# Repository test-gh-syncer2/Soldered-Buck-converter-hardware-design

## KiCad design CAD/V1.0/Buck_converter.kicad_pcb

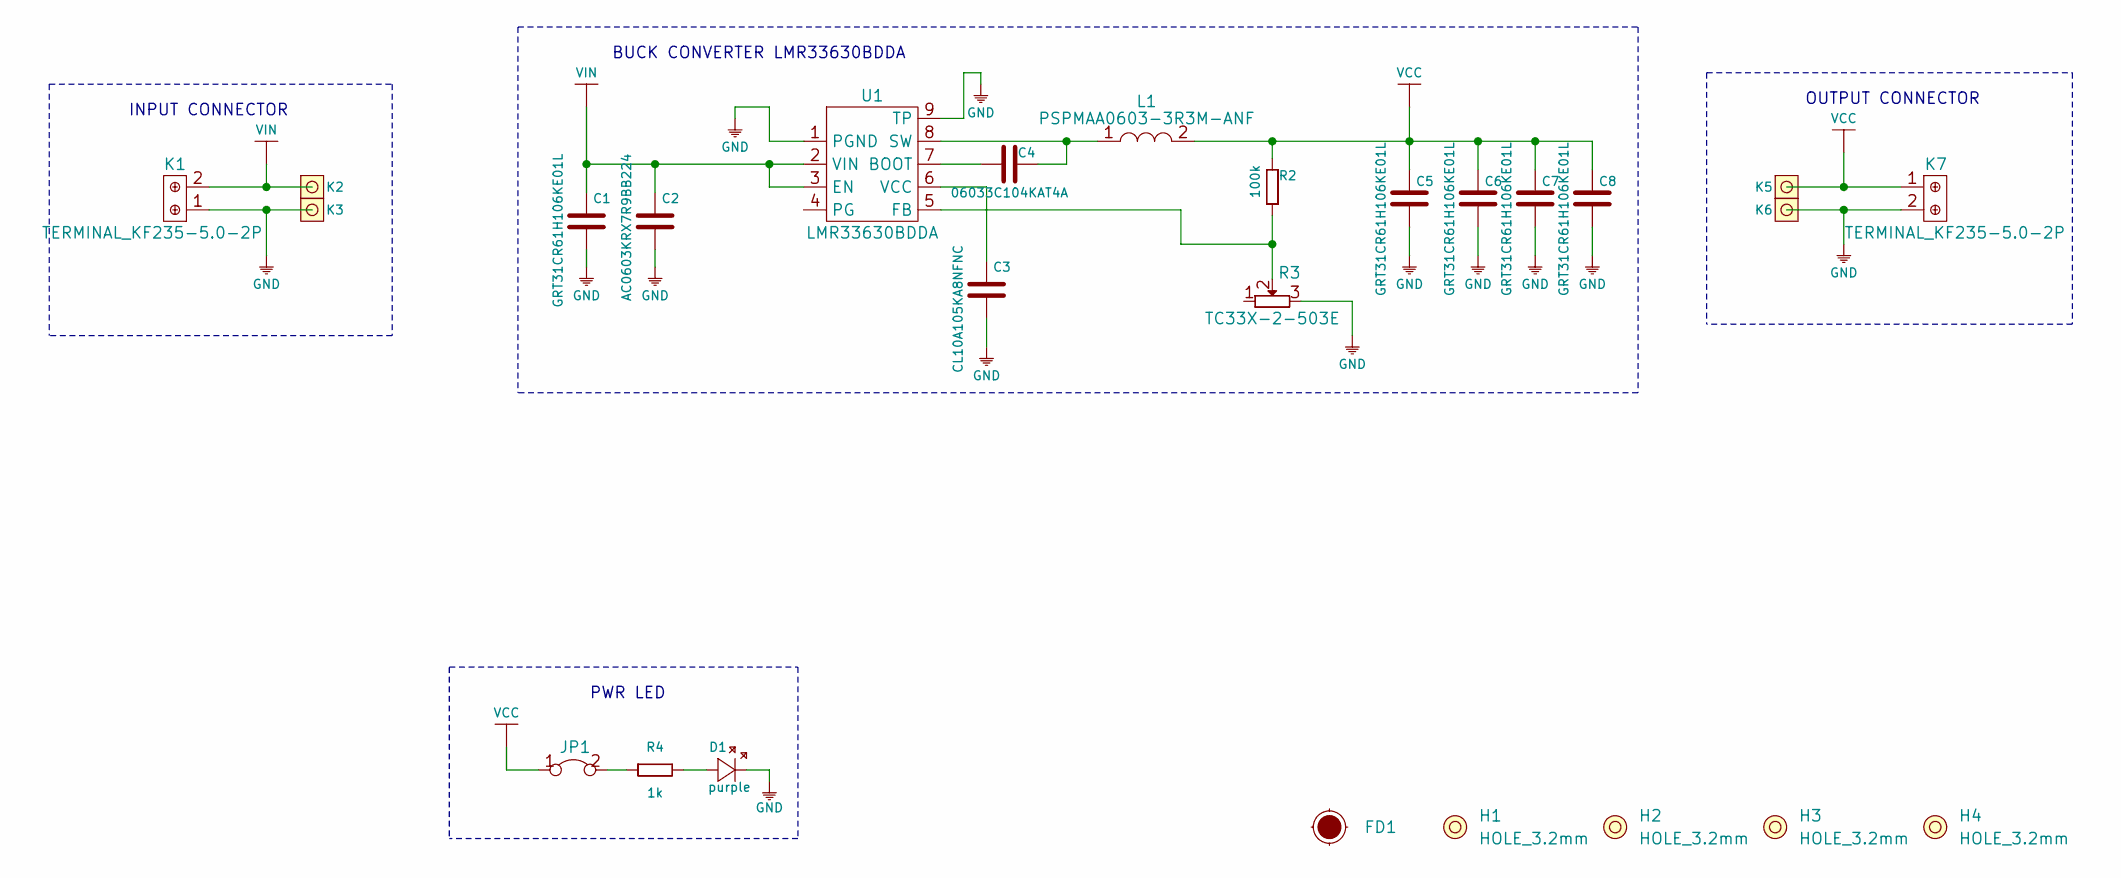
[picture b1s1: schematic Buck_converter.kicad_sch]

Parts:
C1, C5, C6, C7, C8: GRT31CR61H106KE01L; 1206C
C2: AC0603KRX7R9BB224; 0603C
C3: CL10A105KA8NFNC; 0603C
C4: 06033C104KAT4A; 0603C
D1: purple; 0402LED
FD1: Fiducial_Stencil; FIDUCIAL_1MM_PASTE
H1, H2, H3, H4: HOLE_3.2mm
JP1: SMD-JUMPER-CONNECTED_TRACE_NOSLODERMASK
K1, K7: TERMINAL_KF235-5.0-2P
K2, K3, K5, K6: HEADER_MALE_1X1
L1: PSPMAA0603-3R3M-ANF; Inductor_SMD_7x6.6
R2: 100k; 0603R
R3: TC33X-2-503E; tc33x-2-103e
R4: 1k; 0402R
U1: LMR33630BDDA; SOIC-8_POWERPAD

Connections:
GND: C1.1, C2.1, C3.1, C5.1, C6.1, C7.1, C8.1, D1.2 (K), K1.1, K3.1, K6.1, K7.2, R3.3, U1.1 (PGND), U1.9 (TP)
unnamed: C3.2, U1.6 (VCC)
unnamed: C4.1, U1.7 (BOOT)
unnamed: C4.2, L1.1, U1.8 (SW)
unnamed: D1.1 (A), R4.2
unnamed: JP1.2, R4.1
unnamed: R2.1, R3.2, U1.5 (FB)
VCC: C5.2, C6.2, C7.2, C8.2, JP1.1, K5.1, K7.1, L1.2, R2.2
VIN: C1.2, C2.2, K1.2, K2.1, U1.2 (VIN), U1.3 (EN)

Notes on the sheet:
INPUT CONNECTOR
PWR LED
BUCK CONVERTER LMR33630BDDA
OUTPUT CONNECTOR

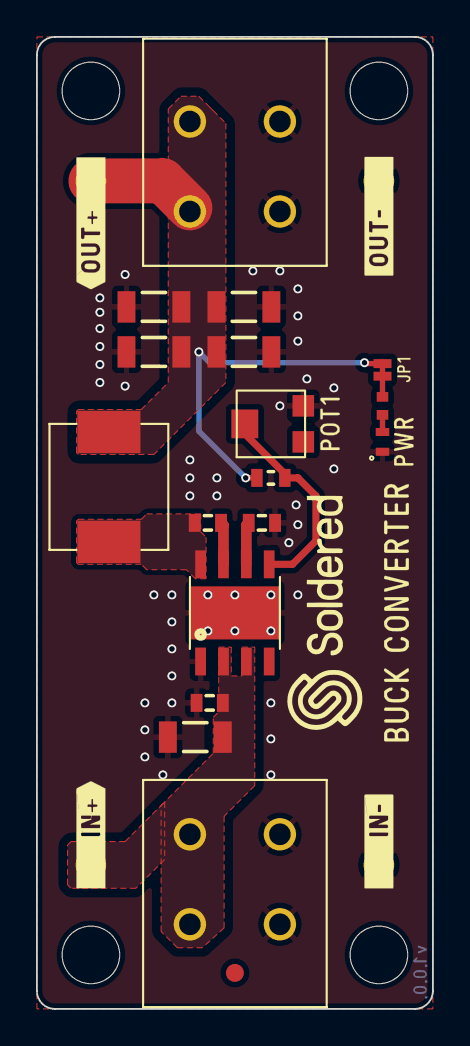
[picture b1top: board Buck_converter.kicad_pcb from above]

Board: 2 copper layers, 22.0 x 54.0 mm, 26 parts (0 on the bottom side), 9 nets.

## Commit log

2021-09-23 Syncing to git
2021-09-23 Updating open source files.
